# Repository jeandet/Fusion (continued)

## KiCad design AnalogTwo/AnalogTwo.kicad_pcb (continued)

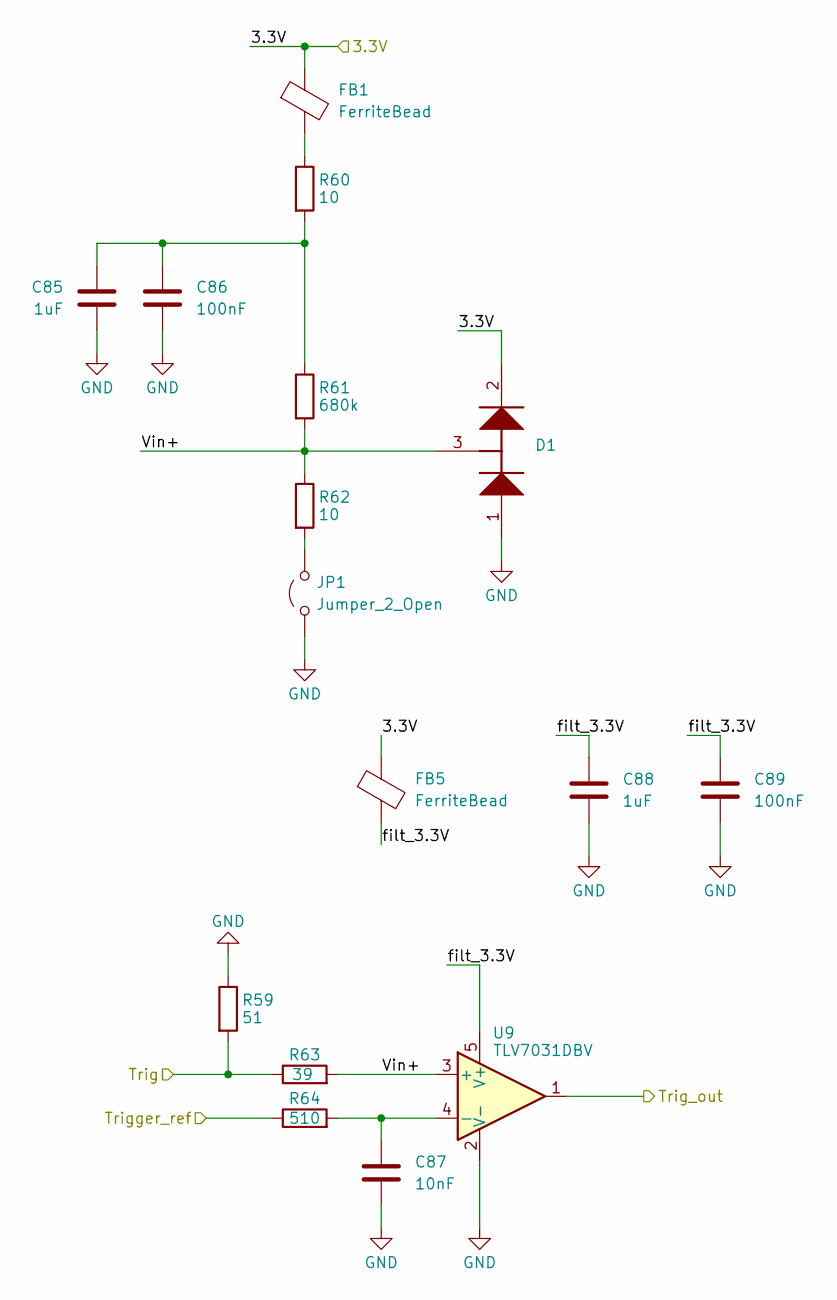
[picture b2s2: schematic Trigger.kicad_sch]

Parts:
C85, C88: 1uF; C_0603_1608Metric_Pad1.08x0.95mm_HandSolder
C86, C89: 100nF; C_0603_1608Metric_Pad1.08x0.95mm_HandSolder
C87: 10nF; C_0603_1608Metric_Pad1.08x0.95mm_HandSolder
D1: SOT-23_Handsoldering
FB1, FB5: FerriteBead; L_Eaton_MCL2012V1
JP1: Jumper_2_Open; SolderJumper-2_P1.3mm_Open_TrianglePad1.0x1.5mm
R59: 51; R_0603_1608Metric_Pad0.98x0.95mm_HandSolder
R60, R62: 10; R_0603_1608Metric_Pad0.98x0.95mm_HandSolder
R61: 680k; R_0603_1608Metric_Pad0.98x0.95mm_HandSolder
R63: 39; R_0603_1608Metric_Pad0.98x0.95mm_HandSolder
R64: 510; R_0603_1608Metric_Pad0.98x0.95mm_HandSolder
U9: TLV7031DBV; SOT-23-5

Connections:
/#3.3V: D1.2 (K), FB1.1, FB5.1; also elsewhere on the board
/DAC_OUT1: R64.1; also elsewhere on the board
/FPGA_BANK0_IO0: U9.1; also elsewhere on the board
/Trigger/Trig: R59.2, R63.1; also elsewhere on the board
/Trigger/Vin+: D1.3 (K/A), R61.2, R62.1, R63.2, U9.3 (+)
/Trigger/filt_3.3V: C88.1, C89.1, FB5.2, U9.5 (V+)
GND: C85.2, C86.2, C87.2, C88.2, C89.2, D1.1 (A), JP1.1 (A), R59.1, U9.2 (V-); also elsewhere on the board
unnamed: C85.1, C86.1, R60.2, R61.1
unnamed: FB1.2, R60.1
unnamed: JP1.2 (B), R62.2
unnamed: C87.1, R64.2, U9.4 (-)

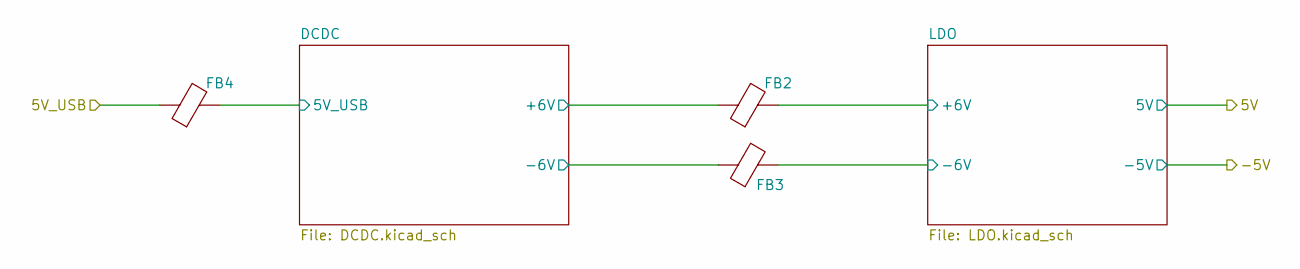
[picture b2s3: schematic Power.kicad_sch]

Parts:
FB2, FB3, FB4: FerriteBead; L_Eaton_MCL2012V1

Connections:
/Power/DCDC/5V_USB: FB4.2; also elsewhere on the board
/Power/DCDC/+6V: FB2.1; also elsewhere on the board
/Power/DCDC/-6V: FB3.1; also elsewhere on the board
/Power/LDO/+6V: FB2.2; also elsewhere on the board
/Power/LDO/-6V: FB3.2; also elsewhere on the board
/USB_5V: FB4.1; also elsewhere on the board

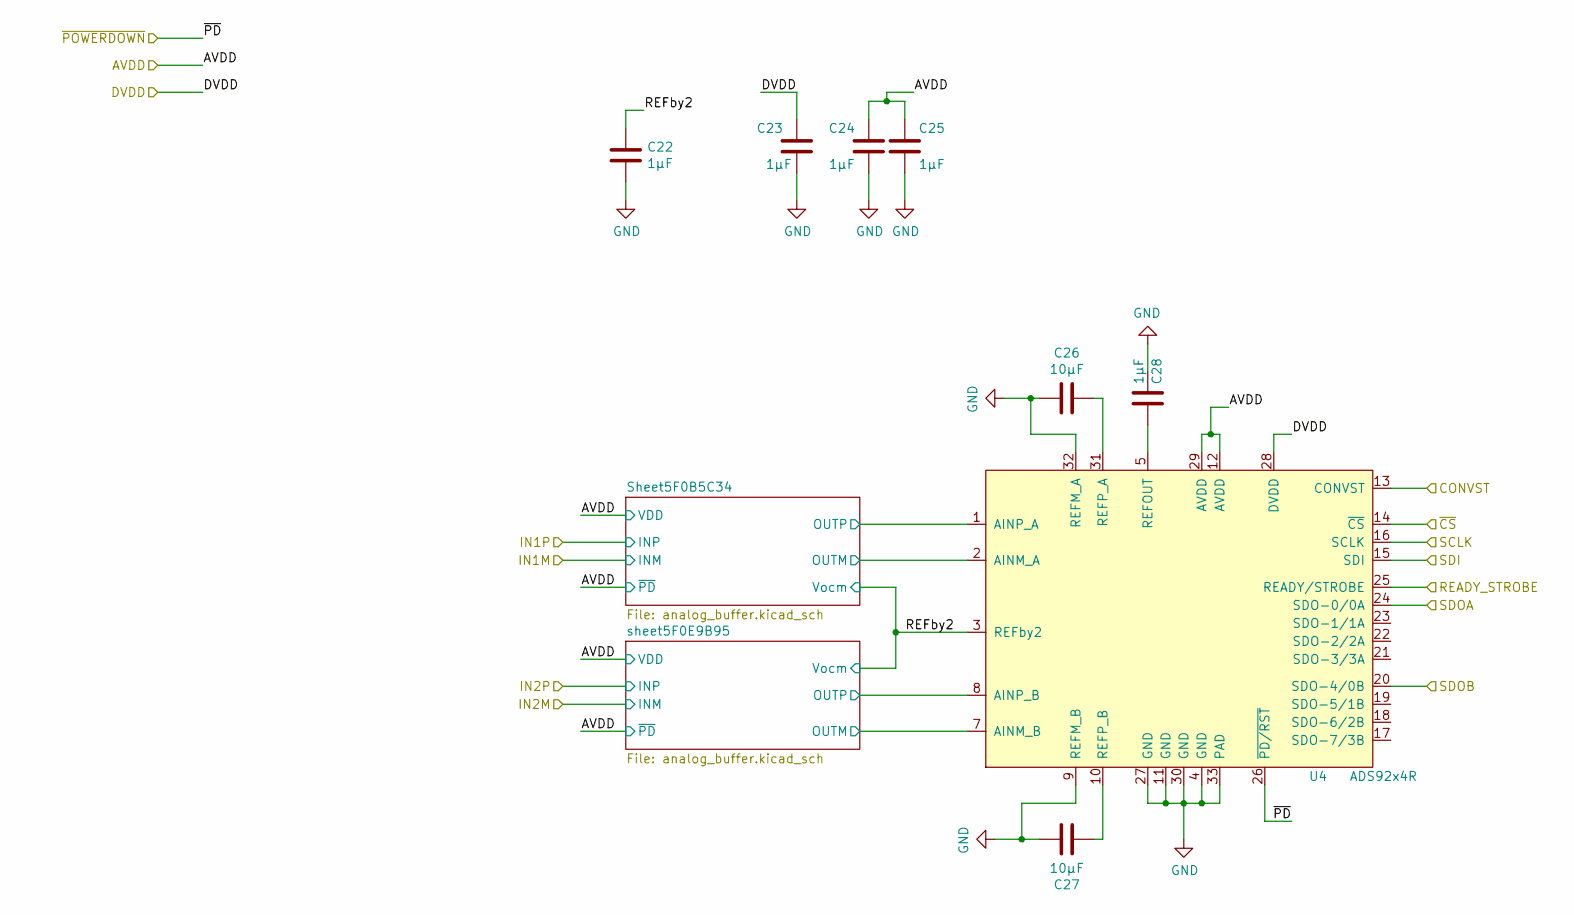
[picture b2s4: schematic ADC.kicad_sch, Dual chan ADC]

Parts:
C22, C23, C24, C25, C28: 1µF; C_0603_1608Metric_Pad1.08x0.95mm_HandSolder
C26, C27: 10µF; C_0805_2012Metric_Pad1.18x1.45mm_HandSolder
U4: ADS92x4R; VQFN-32-1EP_5x5mm_P0.5mm_EP3.1x3.1mm

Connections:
/5V: C24.2, C25.2, U4.12 (AVDD), U4.29 (AVDD); also elsewhere on the board
/#3.3V: C23.2, U4.26 (~PD/RST), U4.28 (DVDD); also elsewhere on the board
/AnalogIn/ADC1/REFby2: C22.1, U4.3 (REFby2); also elsewhere on the board
/AnalogIn/ADC1/Sheet5F0B5C34/OUTM: U4.2 (AINM_A); also elsewhere on the board
/AnalogIn/ADC1/Sheet5F0B5C34/OUTP: U4.1 (AINP_A); also elsewhere on the board
/AnalogIn/ADC1/sheet5F0E9B95/OUTM: U4.7 (AINM_B); also elsewhere on the board
/AnalogIn/ADC1/sheet5F0E9B95/OUTP: U4.8 (AINP_B); also elsewhere on the board
/FPGA_BANK0_IO2: U4.14 (~CS); also elsewhere on the board
/FPGA_BANK0_IO3: U4.13 (CONVST); also elsewhere on the board
/FPGA_BANK0_IO4: U4.16 (SCLK); also elsewhere on the board
/FPGA_BANK0_IO5: U4.15 (SDI); also elsewhere on the board
/FPGA_BANK0_IO6: U4.24 (SDO-0/0A); also elsewhere on the board
/FPGA_BANK0_IO7: U4.20 (SDO-4/0B); also elsewhere on the board
/FPGA_BANK0_IO9: U4.25 (READY/STROBE); also elsewhere on the board
GND: C22.2, C23.1, C24.1, C25.1, C26.1, C27.2, C28.1, U4.4 (GND), U4.9 (REFM_B), U4.11 (GND), U4.27 (GND), U4.30 (GND), U4.32 (REFM_A), U4.33 (PAD); also elsewhere on the board
unnamed: C28.2, U4.5 (REFOUT)
unnamed: C26.2, U4.31 (REFP_A)
unnamed: C27.1, U4.10 (REFP_B)

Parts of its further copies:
C5, C6, C7, C8, C11: 1µF; C_0603_1608Metric_Pad1.08x0.95mm_HandSolder
C9, C10: 10µF; C_0805_2012Metric_Pad1.18x1.45mm_HandSolder
U1: ADS92x4R; VQFN-32-1EP_5x5mm_P0.5mm_EP3.1x3.1mm

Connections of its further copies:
/5V: C7.2, C8.2, U1.12 (AVDD), U1.29 (AVDD); also elsewhere on the board
/#3.3V: C6.2, U1.26 (~PD/RST), U1.28 (DVDD); also elsewhere on the board
/AnalogIn/ADC2/REFby2: C5.1, U1.3 (REFby2); also elsewhere on the board
/AnalogIn/ADC2/Sheet5F0B5C34/OUTM: U1.2 (AINM_A); also elsewhere on the board
/AnalogIn/ADC2/Sheet5F0B5C34/OUTP: U1.1 (AINP_A); also elsewhere on the board
/AnalogIn/ADC2/sheet5F0E9B95/OUTM: U1.7 (AINM_B); also elsewhere on the board
/AnalogIn/ADC2/sheet5F0E9B95/OUTP: U1.8 (AINP_B); also elsewhere on the board
/FPGA_BANK1_IO0: U1.13 (CONVST); also elsewhere on the board
/FPGA_BANK1_IO1: U1.14 (~CS); also elsewhere on the board
/FPGA_BANK1_IO2: U1.15 (SDI); also elsewhere on the board
/FPGA_BANK1_IO3: U1.16 (SCLK); also elsewhere on the board
/FPGA_BANK1_IO4: U1.20 (SDO-4/0B); also elsewhere on the board
/FPGA_BANK1_IO5: U1.24 (SDO-0/0A); also elsewhere on the board
/FPGA_BANK1_IO6: U1.25 (READY/STROBE); also elsewhere on the board
GND: C5.2, C6.1, C7.1, C8.1, C9.1, C10.2, C11.1, U1.4 (GND), U1.9 (REFM_B), U1.11 (GND), U1.27 (GND), U1.30 (GND), U1.32 (REFM_A), U1.33 (PAD); also elsewhere on the board
unnamed: C11.2, U1.5 (REFOUT)
unnamed: C9.2, U1.31 (REFP_A)
unnamed: C10.1, U1.10 (REFP_B)

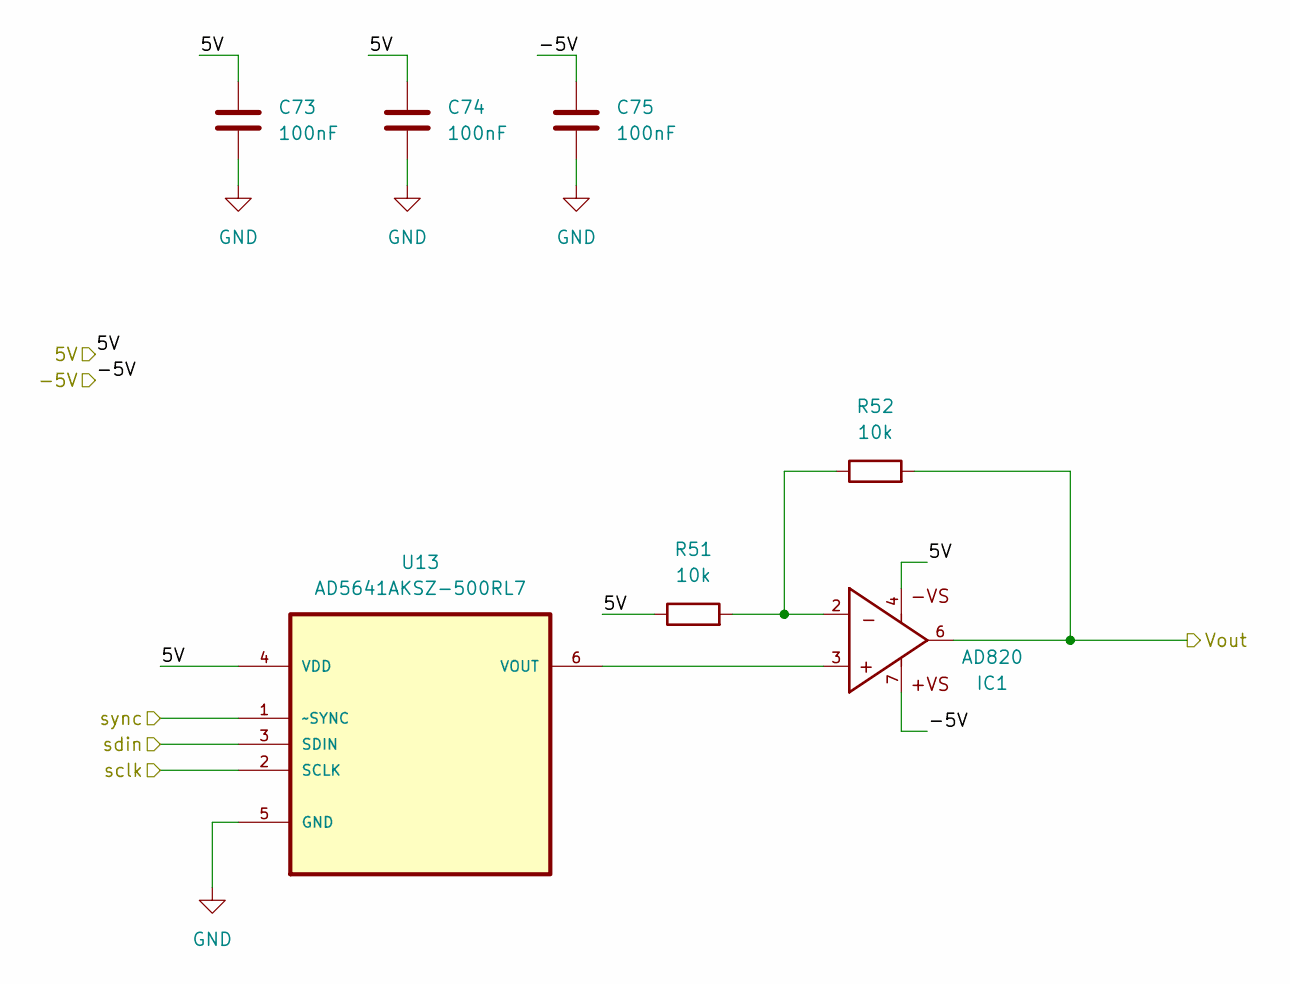
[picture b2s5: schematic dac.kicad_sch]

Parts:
C73, C74, C75: 100nF; C_0603_1608Metric_Pad1.08x0.95mm_HandSolder
IC1: AD820; SOIC-8_3.9x4.9mm_P1.27mm; MPN AD820ARZ
R51, R52: 10k; R_0603_1608Metric_Pad0.98x0.95mm_HandSolder
U13: AD5641AKSZ-500RL7; SC-70-8_Handsoldering; MPN AD5641AKSZ-500RL7

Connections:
/5V: C73.1, C74.1, IC1.4, R51.1, U13.4 (VDD); also elsewhere on the board
/-5V: C75.1, IC1.7; also elsewhere on the board
/AnalogOut/OUT1: IC1.6, R52.2; also elsewhere on the board
/FPGA_BANK7_IO0: U13.2 (SCLK); also elsewhere on the board
/FPGA_BANK7_IO1: U13.3 (SDIN); also elsewhere on the board
/FPGA_BANK7_IO3: U13.1 (~SYNC); also elsewhere on the board
GND: C73.2, C74.2, C75.2, U13.5 (GND); also elsewhere on the board
unnamed: IC1.2, R51.2, R52.1
unnamed: IC1.3, U13.6 (VOUT)

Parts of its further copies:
C76, C77, C78: 100nF; C_0603_1608Metric_Pad1.08x0.95mm_HandSolder
IC2: AD820; SOIC-8_3.9x4.9mm_P1.27mm; MPN AD820ARZ
R53, R54: 10k; R_0603_1608Metric_Pad0.98x0.95mm_HandSolder
U14: AD5641AKSZ-500RL7; SC-70-8_Handsoldering; MPN AD5641AKSZ-500RL7

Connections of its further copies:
/5V: C76.1, C77.1, IC2.4, R53.1, U14.4 (VDD); also elsewhere on the board
/-5V: C78.1, IC2.7; also elsewhere on the board
/AnalogOut/OUT2: IC2.6, R54.2; also elsewhere on the board
/FPGA_BANK1_IO12: U14.3 (SDIN); also elsewhere on the board
/FPGA_BANK1_IO13: U14.2 (SCLK); also elsewhere on the board
/FPGA_BANK1_IO15: U14.1 (~SYNC); also elsewhere on the board
GND: C76.2, C77.2, C78.2, U14.5 (GND); also elsewhere on the board
unnamed: IC2.2, R53.2, R54.1
unnamed: IC2.3, U14.6 (VOUT)

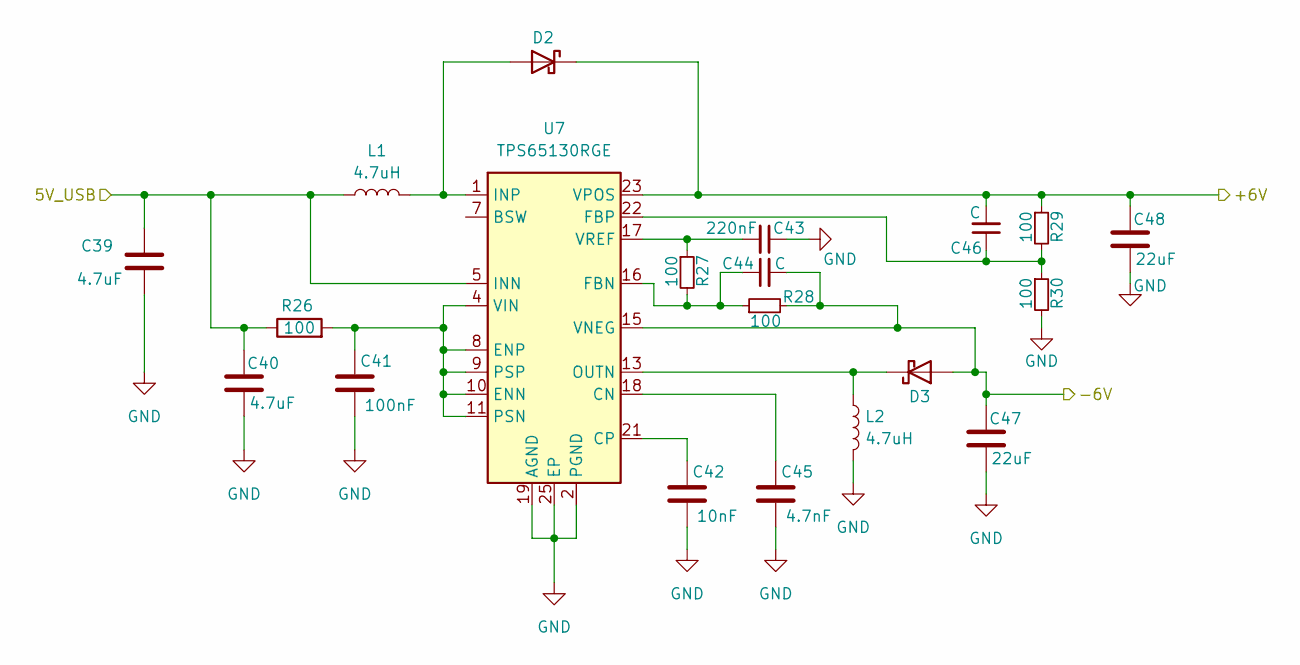
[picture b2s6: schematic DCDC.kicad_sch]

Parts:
C39, C40: 4.7uF; C_1206_3216Metric_Pad1.33x1.80mm_HandSolder
C41: 100nF; C_0402_1005Metric_Pad0.74x0.62mm_HandSolder
C42: 10nF; C_0402_1005Metric_Pad0.74x0.62mm_HandSolder
C43: 220nF; C_0402_1005Metric_Pad0.74x0.62mm_HandSolder
C44, C46: C; C_0402_1005Metric_Pad0.74x0.62mm_HandSolder
C45: 4.7nF; C_0402_1005Metric_Pad0.74x0.62mm_HandSolder
C47, C48: 22uF; C_1206_3216Metric_Pad1.33x1.80mm_HandSolder
D2, D3: D_Schottky; D_Powermite2_AK
L1: 4.7uH; L_7.3x7.3_H3.5
L2: 4.7uH; L_7.3x7.3_H3.5; mouser mouser https://eu.mouser.com/ProductDet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
R26, R27, R28, R29, R30: 100; R_0402_1005Metric_Pad0.72x0.64mm_HandSolder
U7: TPS65130RGE; VQFN-24-1EP_4x4mm_P0.5mm_EP2.45x2.45mm_ThermalVias

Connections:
/Power/DCDC/5V_USB: C39.1, C40.1, L1.1, R26.1, U7.5 (INN), U7.6 (INN); also elsewhere on the board
/Power/DCDC/+6V: C46.2, C48.1, D2.1 (K), R29.1, U7.23 (VPOS); also elsewhere on the board
/Power/DCDC/-6V: C44.2, C47.1, D3.2 (A), R28.2, U7.15 (VNEG); also elsewhere on the board
GND: C39.2, C40.2, C41.2, C42.2, C43.1, C45.2, C47.2, C48.2, L2.2, R30.2, U7.2 (PGND), U7.3 (PGND), U7.19 (AGND), U7.25 (EP); also elsewhere on the board
unnamed: D2.2 (A), L1.2, U7.1 (INP), U7.24 (INP)
unnamed: D3.1 (K), L2.1, U7.13 (OUTN), U7.14 (OUTN)
unnamed: C45.1, U7.18 (CN)
unnamed: C42.1, U7.21 (CP)
unnamed: C41.1, R26.2, U7.4 (VIN), U7.8 (ENP), U7.9 (PSP), U7.10 (ENN), U7.11 (PSN)
unnamed: C44.1, R27.2, R28.1, U7.16 (FBN)
unnamed: C46.1, R29.2, R30.1, U7.22 (FBP)
unnamed: C43.2, R27.1, U7.17 (VREF)

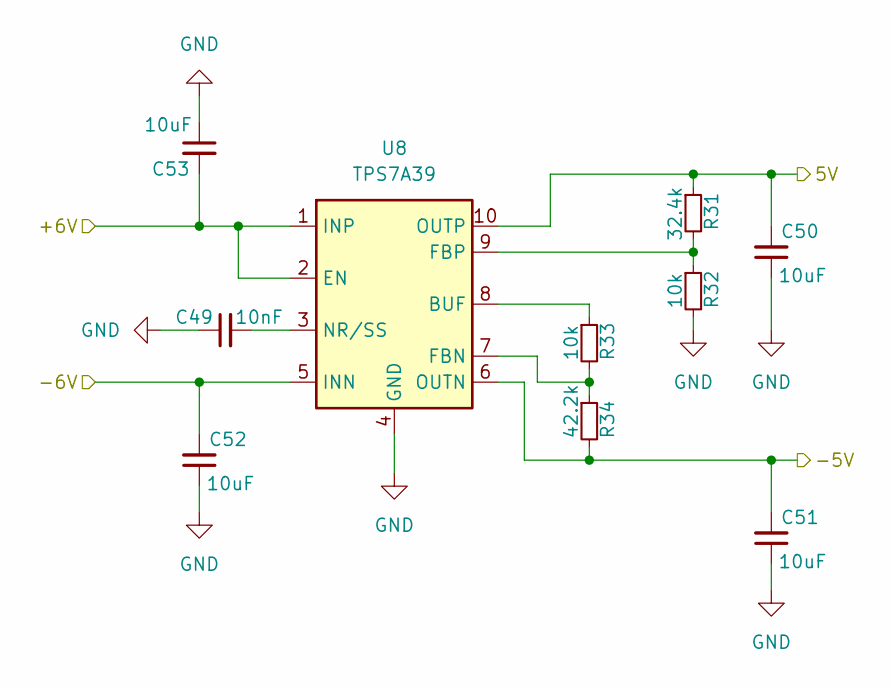
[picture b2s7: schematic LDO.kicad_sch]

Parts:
C49: 10nF; C_0603_1608Metric_Pad1.08x0.95mm_HandSolder
C50, C51, C52, C53: 10uF; C_1206_3216Metric_Pad1.33x1.80mm_HandSolder
R31: 32.4k; R_0402_1005Metric_Pad0.72x0.64mm_HandSolder
R32, R33: 10k; R_0402_1005Metric_Pad0.72x0.64mm_HandSolder
R34: 42.2k; R_0402_1005Metric_Pad0.72x0.64mm_HandSolder
U8: TPS7A39; Texas_S-PVSON-N10_ThermalVias

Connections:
/5V: C50.2, R31.1, U8.10 (OUTP); also elsewhere on the board
/-5V: C51.2, R34.2, U8.6 (OUTN); also elsewhere on the board
/Power/LDO/+6V: C53.2, U8.1 (INP), U8.2 (EN); also elsewhere on the board
/Power/LDO/-6V: C52.2, U8.5 (INN); also elsewhere on the board
GND: C49.1, C50.1, C51.1, C52.1, C53.1, R32.2, U8.4 (GND), U8.11 (GND); also elsewhere on the board
unnamed: R33.1, U8.8 (BUF)
unnamed: R33.2, R34.1, U8.7 (FBN)
unnamed: R31.2, R32.1, U8.9 (FBP)
unnamed: C49.2, U8.3 (NR/SS)

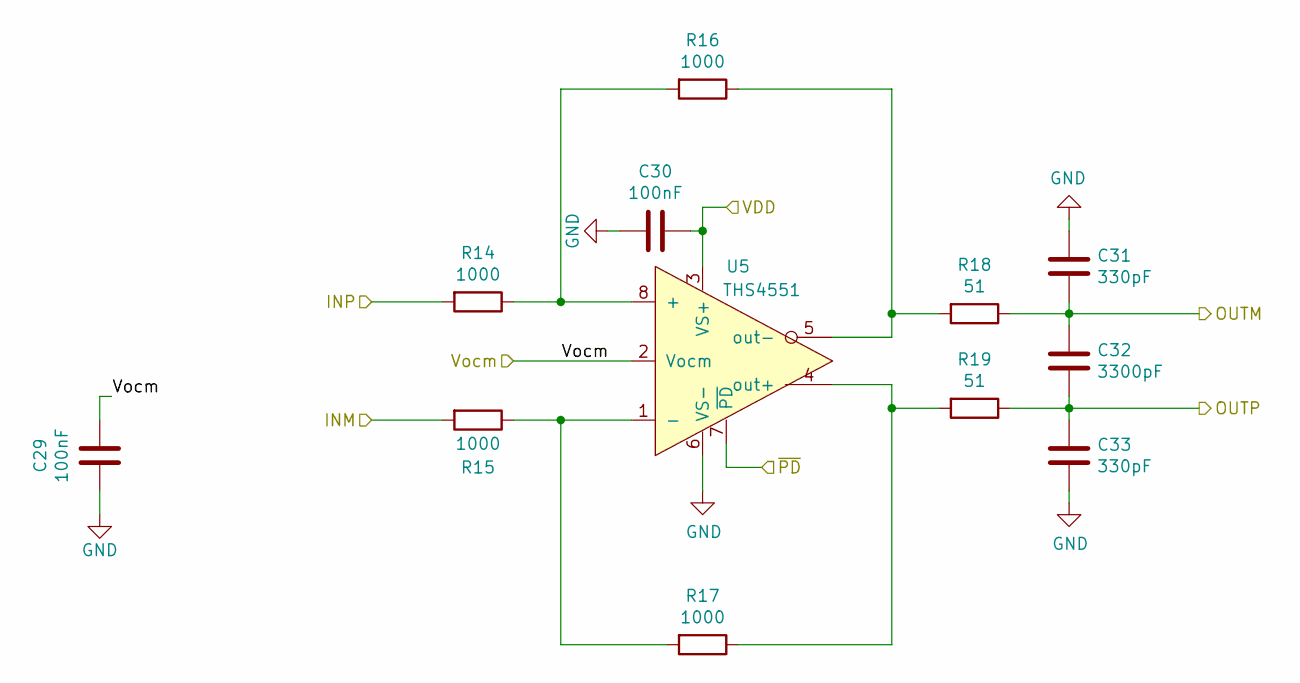
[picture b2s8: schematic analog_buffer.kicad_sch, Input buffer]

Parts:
C29, C30: 100nF; C_0603_1608Metric_Pad1.08x0.95mm_HandSolder
C31, C33: 330pF; C_0603_1608Metric_Pad1.08x0.95mm_HandSolder
C32: 3300pF; C_0603_1608Metric_Pad1.08x0.95mm_HandSolder
R14, R15, R16, R17: 1000; R_0603_1608Metric_Pad0.98x0.95mm_HandSolder
R18, R19: 51; R_0603_1608Metric_Pad0.98x0.95mm_HandSolder
U5: THS4551; VSSOP-8_3.0x3.0mm_P0.65mm

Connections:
/5V: C30.1, U5.3 (VS+), U5.7 (~PD); also elsewhere on the board
/AnalogIn/ADC1/REFby2: C29.1, U5.2 (Vocm); also elsewhere on the board
/AnalogIn/ADC1/Sheet5F0B5C34/OUTM: C31.2, C32.1, R18.1; also elsewhere on the board
/AnalogIn/ADC1/Sheet5F0B5C34/OUTP: C32.2, C33.1, R19.1; also elsewhere on the board
/AnalogIn/IN1M: R15.2; also elsewhere on the board
/AnalogIn/IN1P: R14.2; also elsewhere on the board
GND: C29.2, C30.2, C31.1, C33.2, U5.6 (VS-); also elsewhere on the board
unnamed: R14.1, R16.2, U5.8 (+)
unnamed: R15.1, R17.2, U5.1 (-)
unnamed: R17.1, R19.2, U5.4 (out+)
unnamed: R16.1, R18.2, U5.5 (out-)

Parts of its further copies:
C12, C13, C17, C18, C34, C35: 100nF; C_0603_1608Metric_Pad1.08x0.95mm_HandSolder
C14, C16, C19, C21, C36, C38: 330pF; C_0603_1608Metric_Pad1.08x0.95mm_HandSolder
C15, C20, C37: 3300pF; C_0603_1608Metric_Pad1.08x0.95mm_HandSolder
R2, R3, R4, R5, R8, R9, R10, R11, R20, R21, R22, R23: 1000; R_0603_1608Metric_Pad0.98x0.95mm_HandSolder
R6, R7, R12, R13, R24, R25: 51; R_0603_1608Metric_Pad0.98x0.95mm_HandSolder
U2, U3, U6: THS4551; VSSOP-8_3.0x3.0mm_P0.65mm

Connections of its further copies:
/5V: C13.1, C18.1, C35.1, U2.3 (VS+), U2.7 (~PD), U3.3 (VS+), U3.7 (~PD), U6.3 (VS+), U6.7 (~PD); also elsewhere on the board
/AnalogIn/ADC1/REFby2: C34.1, U6.2 (Vocm); also elsewhere on the board
/AnalogIn/ADC1/sheet5F0E9B95/OUTM: C36.2, C37.1, R24.1; also elsewhere on the board
/AnalogIn/ADC1/sheet5F0E9B95/OUTP: C37.2, C38.1, R25.1; also elsewhere on the board
/AnalogIn/ADC2/REFby2: C12.1, C17.1, U2.2 (Vocm), U3.2 (Vocm); also elsewhere on the board
/AnalogIn/ADC2/Sheet5F0B5C34/OUTM: C14.2, C15.1, R6.1; also elsewhere on the board
/AnalogIn/ADC2/Sheet5F0B5C34/OUTP: C15.2, C16.1, R7.1; also elsewhere on the board
/AnalogIn/ADC2/sheet5F0E9B95/OUTM: C19.2, C20.1, R12.1; also elsewhere on the board
/AnalogIn/ADC2/sheet5F0E9B95/OUTP: C20.2, C21.1, R13.1; also elsewhere on the board
/AnalogIn/IN2M: R21.2; also elsewhere on the board
/AnalogIn/IN2P: R20.2; also elsewhere on the board
/AnalogIn/IN3M: R3.2; also elsewhere on the board
/AnalogIn/IN3P: R2.2; also elsewhere on the board
/AnalogIn/IN4M: R9.2; also elsewhere on the board
/AnalogIn/IN4P: R8.2; also elsewhere on the board
GND: C12.2, C13.2, C14.1, C16.2, C17.2, C18.2, C19.1, C21.2, C34.2, C35.2, C36.1, C38.2, U2.6 (VS-), U3.6 (VS-), U6.6 (VS-); also elsewhere on the board
unnamed: R2.1, R4.2, U2.8 (+)
unnamed: R3.1, R5.2, U2.1 (-)
unnamed: R5.1, R7.2, U2.4 (out+)
unnamed: R4.1, R6.2, U2.5 (out-)
unnamed: R8.1, R10.2, U3.8 (+)
unnamed: R9.1, R11.2, U3.1 (-)
unnamed: R11.1, R13.2, U3.4 (out+)
unnamed: R10.1, R12.2, U3.5 (out-)
unnamed: R20.1, R22.2, U6.8 (+)
unnamed: R21.1, R23.2, U6.1 (-)
unnamed: R23.1, R25.2, U6.4 (out+)
unnamed: R22.1, R24.2, U6.5 (out-)

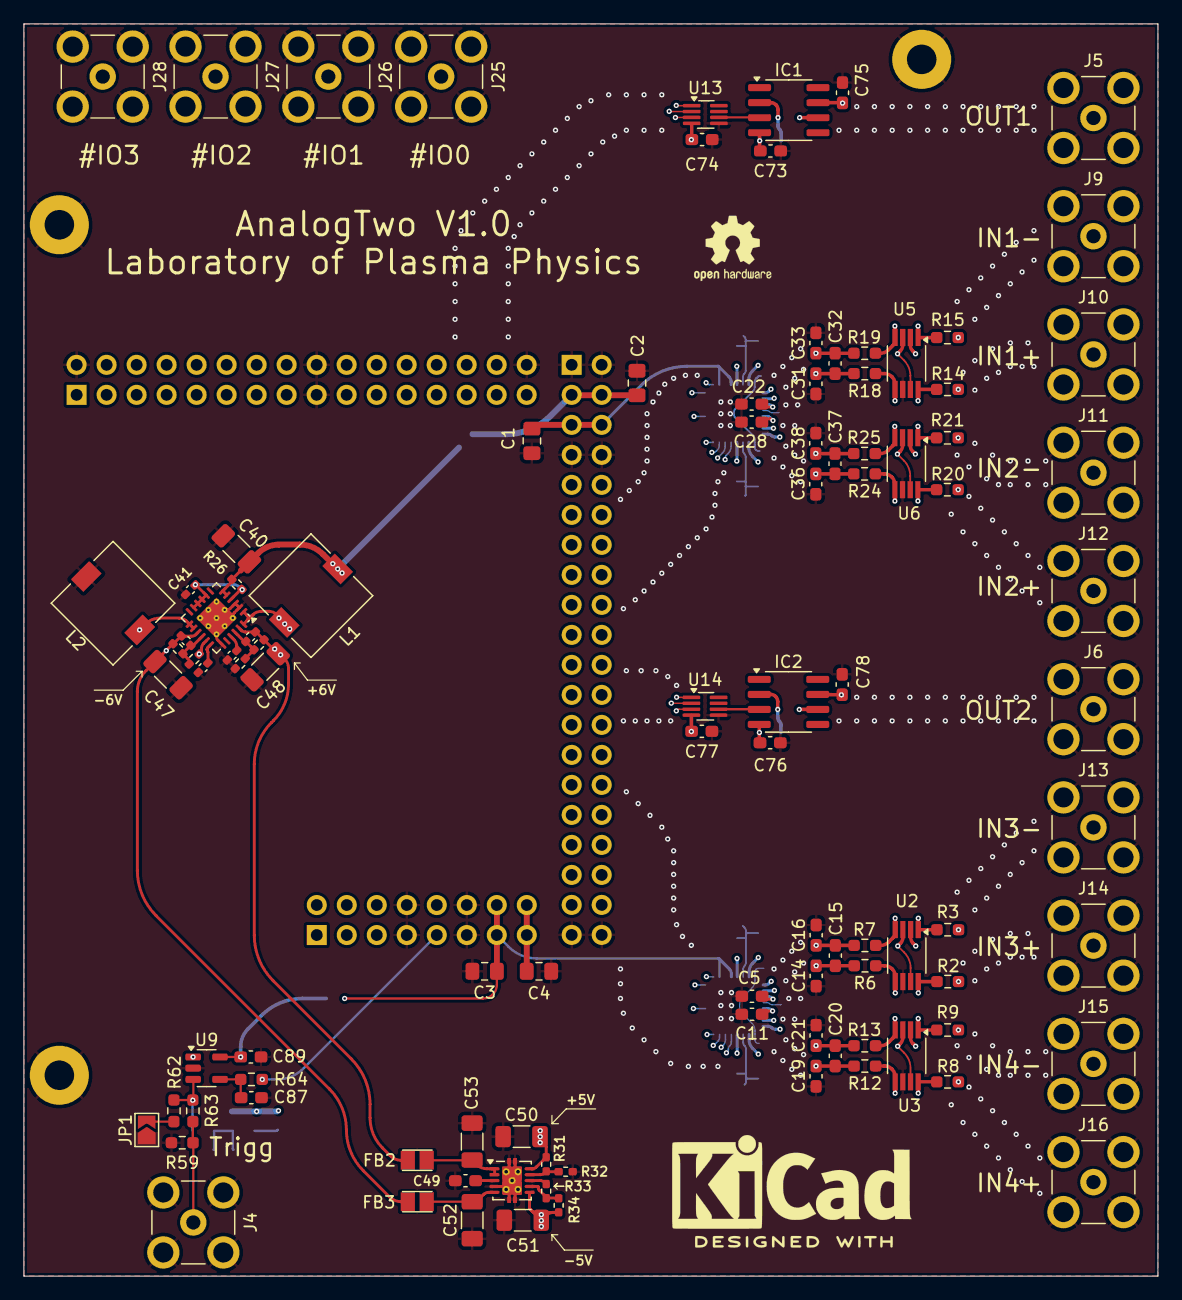
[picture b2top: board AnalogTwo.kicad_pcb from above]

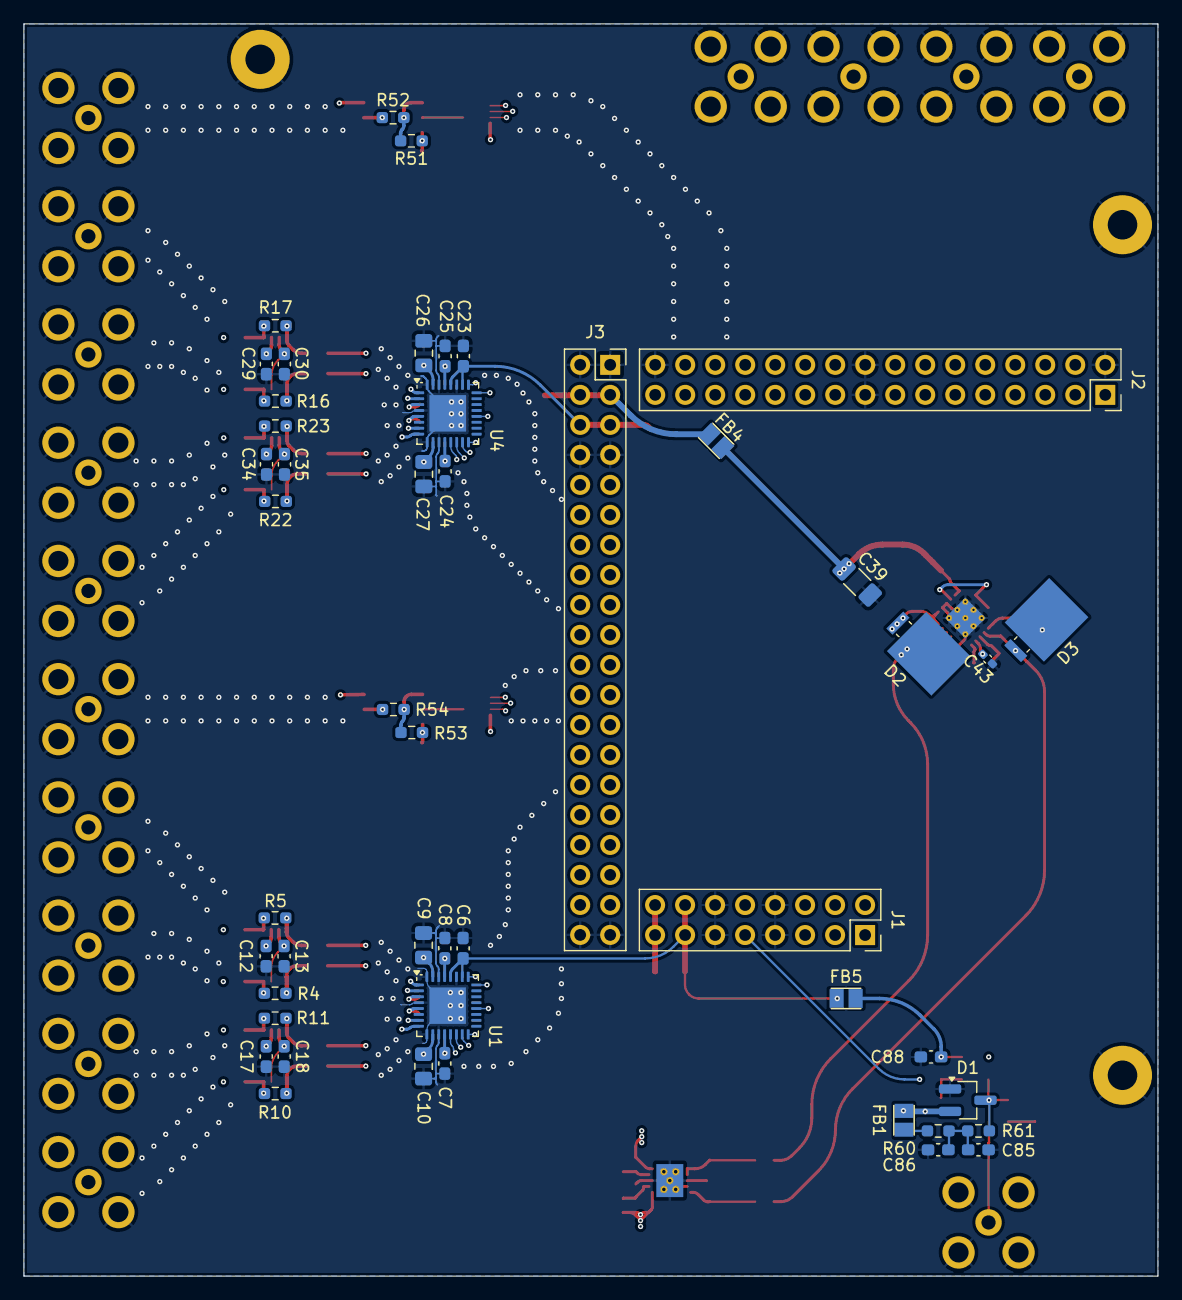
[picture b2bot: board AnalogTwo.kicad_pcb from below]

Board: 4 copper layers, 96.0 x 106.0 mm, 149 parts (48 on the bottom side), 104 nets.
